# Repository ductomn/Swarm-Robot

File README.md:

# Swarm Robot Platform

A low-cost, scalable swarm robotic platform designed for research and educational purposes, capable of infrared (IR)-based communication and basic cooperative behaviors.

Playlist of videos showcasing robots and algorithms: https://www.youtube.com/playlist?list=PLNTM9zCJujTltedypfpow2rPiPkVAqfGI

---

## 🧠 About the Project

This project focuses on the design of a **cooperative robotic platform** built around the ESP32 microcontroller. The primary goal is to enable simple, local communication and decentralized coordination among identical robots, forming a **swarm**.

**Key design constraints:**
- Minimal production cost (~24 EUR/robot, parts only)
- Compact and robust mechanical design
- Infrared-based full-duplex communication (360°)
- Modular and scalable C firmware using ESP-IDF
- Developed as part of a Bachelor’s Thesis at Brno University of Technology

> **Thesis Title:**  
> *Návrh a realizace kooperativní robotické platformy s jednoduchou komunikací*  
> (*Design and Implementation of a Cooperative Robotic Platform with Simple Communication*)

---

## ⚙️ Features

### 🔁 360° IR Communication
6 pairs of IR LEDs and phototransistors evenly placed around the robot enable full directional communication.

### 🚧 Obstacle Detection
2 front-facing IR LED + phototransistor pairs detect obstacles.

### 🤖 Cooperative Algorithms

#### With Leader
- Simulates a robot "calling" others to complete a task.
- Modified CSMA/CA protocol ensures robots check for ongoing transmissions before broadcasting.
- Robots walk randomly looking for signals:
  - If signal is found in a randomly chosen time window → the robot becomes a **follower**.
  - If not → the robot becomes a **leader**.
- **Leader** can be pre-set (WITH_LEADER 1)

- **Flowchart of system with leader:**

- **Implemented algorithms:**

  - **Follow**  
    Followers track the leader, who moves randomly.  

  - **Spread Out**  
    Leader stays in place and acts as a beacon. Followers spread and return.  

#### Without Leader
- No signal detection or leader election.
- Algorithms run immediately after power-on.
  
- **Implemented algorithms:**

  - **Follow Chain**  
    Robots follow each other in a line. First robot walks randomly. Predefined or dynamic ID (order) assignment.  

  - **Chain**  
    Robots stay still in a line. The last robot moves forward to the front.  

### 🧠 FSM-Controlled Behavior

Each robot uses a finite state machine (FSM) for autonomous control and decision-making. The diagram shows the flow of states of algorithms with leader.  

### 🔧 Firmware Modules

- `io_define` – I/O pin mappings, robot ID
- `servo_driver` – movement (servo) control
- `led_driver` – IR LED driver
- `hwtimer` – Hardware timer driver
- `adc_lib` – ADC driver
- `dm_comm` – IR communication (Manchester encoding, CSMA/CA)
- `coop` – Cooperative algorithm logic
- `state_machine` – FSM and behavior transitions

---

## 🛠️ Setting Up

### Requirements

- [ESP-IDF](https://docs.espressif.com/projects/esp-idf/en/latest/esp32/)
- PlatformIO (recommended; VS Code plugin)  
  Target board: `ESP32DOIT-DEVKIT-V1`
- USB-to-UART bridge (e.g. CP2102)

### 🔧 Calibration  

- **Movement Calibration**  
  The robot doesn’t use encoders, so the motors may spin at different speeds, causing drift.  
  Adjust `SERVO_FORWARD_LEFT_MOD` and `SERVO_BACKWARDS_RIGHT_MOD` in `io_define.h` to straighten movement.

- **IR Signal Thresholds**  
  Tune `SIG_THRESHOLD` in `dm_comm.h` and `DIS_THRESHOLD` in `coop.h` to adjust signal sensitivity.

- **Algorithm Selection**  
  Some algorithms (like **Chain** or **Follow Chain**) should start immediately on power-up.  
  Define the startup behavior by setting flags to "1" (`CHAIN` or `FOLLOW_CHAIN`).

### ⚡ Flashing Instructions  

1. Connect the robot to your computer via USB.
2. Open `io_define.h` and set:
   - `ROBOT_ID` – unique number per robot
   - `WITH_LEADER` – `1` (for pre-set leader - ID1) or `0`
   - `CHAIN` or `FOLLOW_CHAIN` – chosen algorithm
3. Build and flash the firmware

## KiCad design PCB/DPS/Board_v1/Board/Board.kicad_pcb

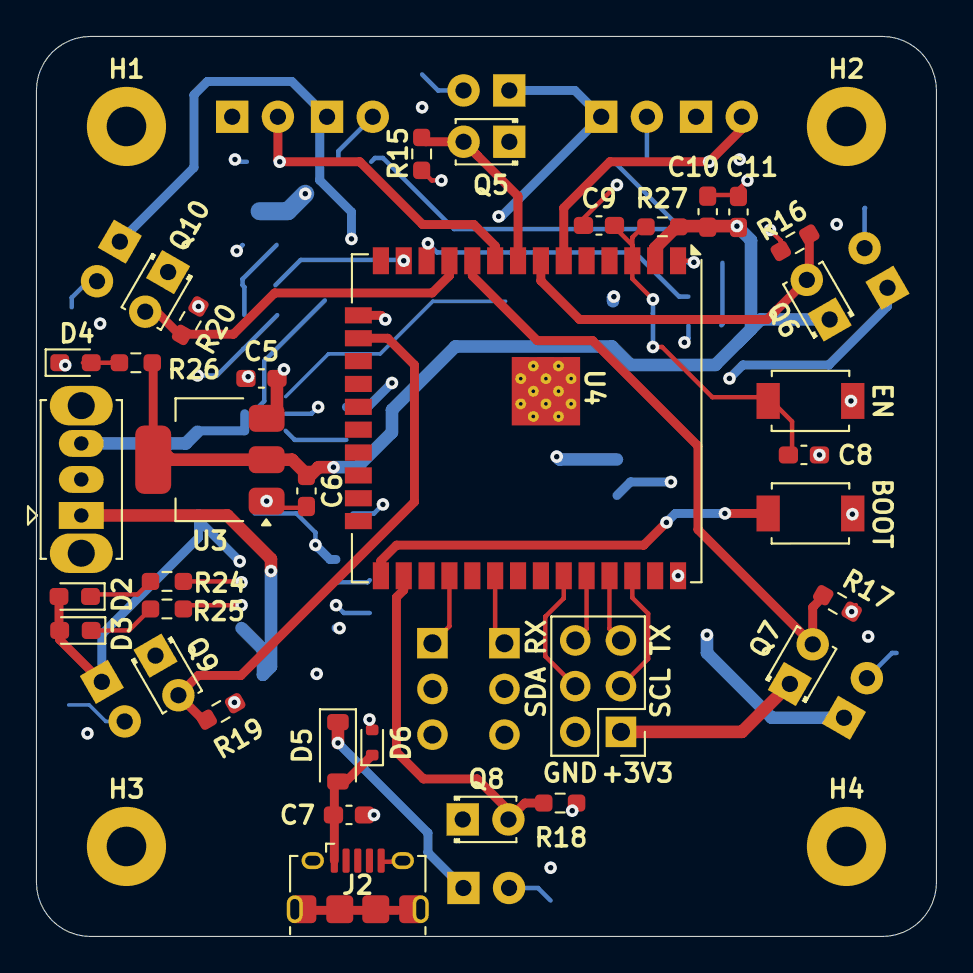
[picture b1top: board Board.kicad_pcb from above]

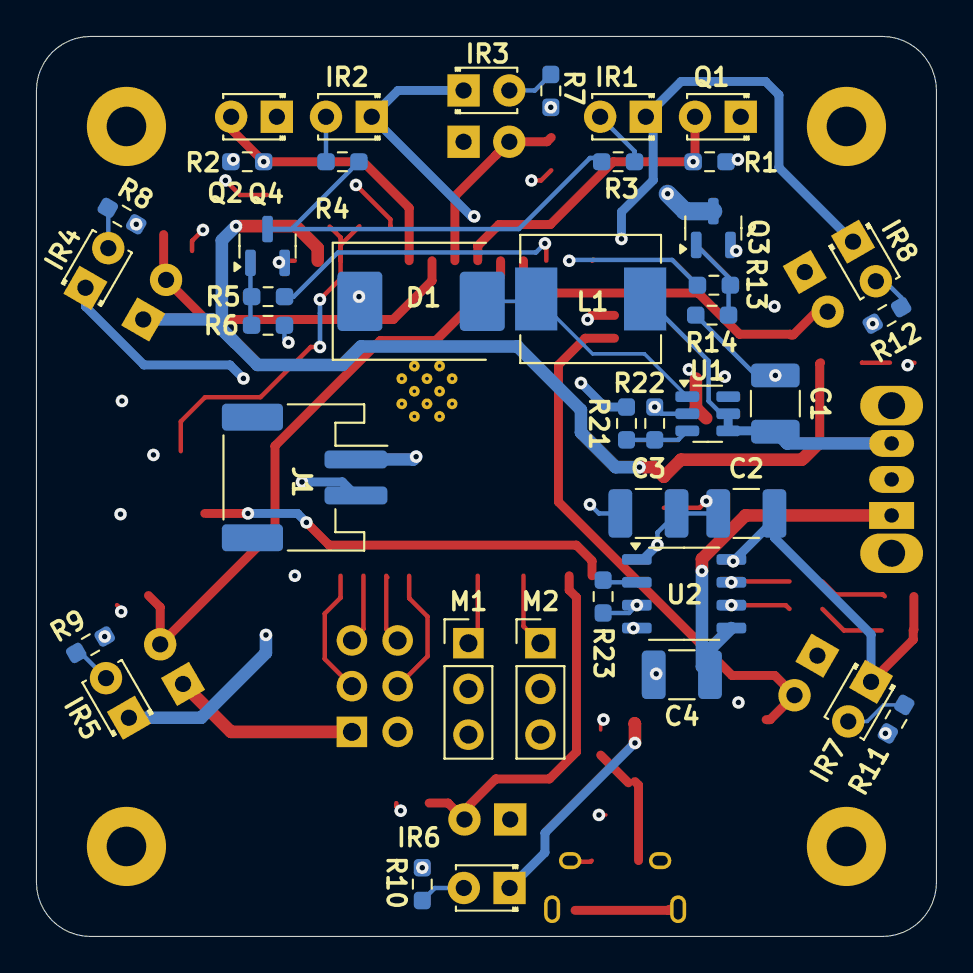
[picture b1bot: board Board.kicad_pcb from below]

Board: 4 copper layers, 50.0 x 50.0 mm, 79 parts (40 on the bottom side), 45 nets.

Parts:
BOOT: TS-1088R-02026; SW_Tactile_TS-1088R-02026
C1, C2: 22uF; C_1210_3225Metric_Pad1.33x2.70mm_HandSolder
C3, C4: 10uF; C_1210_3225Metric_Pad1.33x2.70mm_HandSolder
C5, C6: 10uF; C_0603_1608Metric_Pad1.08x0.95mm_HandSolder
C7, C8, C9, C11: 0.1uF; C_0603_1608Metric_Pad1.08x0.95mm_HandSolder
C10: 22uF; C_0603_1608Metric_Pad1.08x0.95mm_HandSolder
Comms1: PinHeader_2x03_P2.54mm_Vertical
D1: D_Schottky; D_SMC
D2: LED_RED; LED_0603_1608Metric_Pad1.05x0.95mm_HandSolder
D3: LED_GREEN; LED_0603_1608Metric_Pad1.05x0.95mm_HandSolder
D4: LED; LED_0603_1608Metric_Pad1.05x0.95mm_HandSolder
D5: 1N5819HW-7-F; D_SOD-123
D6: ESD5Z5.0T1G; D_SOD-523
EN: TS-1088R-02026; SW_Tactile_TS-1088R-02026
H1, H2, H3, H4: MountingHole_Pad; MountingHole_2.2mm_M2_Pad
IR1, IR2: SFH4544; LED_D1.8mm_W3.3mm_H2.4mm
IR3, IR4, IR5, IR6, IR7, IR8: OED-EL-1L2; LED_D1.8mm_W3.3mm_H2.4mm
J1: Li-Po 3.7V; JST_PH_S2B-PH-SM4-TB_1x02-1MP_P2.00mm_Horizontal
J2: USB_B_Micro; USB_Micro-B_Amphenol_10118194_Horizontal
L1: 4.7uH; L_Chilisin_BMRx00060630
M1, M2: SG90; PinHeader_1x03_P2.54mm_Vertical
Q1, Q2, Q5, Q6, Q7, Q8, Q9, Q10: TEFT4300; LED_D1.8mm_W3.3mm_H2.4mm
Q3, Q4: SI2312CDS; SOT-23
R1, R2, R15, R16, R17, R18, R19, R20: 4k7; R_0603_1608Metric_Pad0.98x0.95mm_HandSolder
R3, R4, R7, R8, R9, R10, R11, R12: 39; R_0603_1608Metric_Pad0.98x0.95mm_HandSolder
R5, R13: 100; R_0603_1608Metric_Pad0.98x0.95mm_HandSolder
R6, R14: 47k; R_0603_1608Metric_Pad0.98x0.95mm_HandSolder
R21: 16k; R_0603_1608Metric_Pad0.98x0.95mm_HandSolder
R22: 2k2; R_0603_1608Metric_Pad0.98x0.95mm_HandSolder
R23: 1k2; R_0603_1608Metric_Pad0.98x0.95mm_HandSolder
R24, R25: 1k; R_0603_1608Metric_Pad0.98x0.95mm_HandSolder
R26: 5k1; R_0603_1608Metric_Pad0.98x0.95mm_HandSolder
R27: 10k; R_0603_1608Metric_Pad0.98x0.95mm_HandSolder
SW1: SLW-864574-5A-RA-N-D; SW_Slide_SPDT_Straight_CK_OS102011MS2Q
U1: MT3608; SOT-23-6
U2: TP4056; SOP-8_3.9x4.9mm_P1.27mm
U3: AMS1117-3.3; SOT-223-3_TabPin2
U4: ESP32-WROOM-32UE

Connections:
+3V3: C6.1, C10.1, C11.1, Comms1.1 (VCC), Q1.1 (C), Q2.1 (C), Q5.1 (C), Q6.1 (C), Q7.1 (C), Q8.1 (C), Q9.1 (C), Q10.1 (C), R26.1, R27.1, U3.2 (VO), U4.2 (VDD)
+5V: C2.1, C3.1, C5.1, D1.1 (K), D2.2 (A), D3.2 (A), D5.1 (K), IR1.1 (K), IR2.1 (K), IR3.1 (K), IR4.1 (K), IR5.1 (K), IR6.1 (K), IR7.1 (K), IR8.1 (K), M1.2 (+), M2.2 (+), R21.1, U2.4 (VCC), U2.8 (CE), U3.3 (VI)
/ESP32/EN: C8.1, C9.1, EN.2, R27.2, U4.3 (EN)
/ESP32/IO0_BTN: BOOT.2, U4.25 (IO0)
A0: Q5.2 (E), R15.2, U4.8 (IO32)
A1: Q6.2 (E), R16.2, U4.7 (IO35)
A2: Q7.2 (E), R17.2, U4.10 (IO25)
A3: Q8.2 (E), R18.2, U4.26 (IO4)
A4: Q9.2 (E), R19.2, U4.16 (IO13)
A5: Q10.2 (E), R20.2, U4.11 (IO26)
A8_DIS: Q1.2 (E), R1.2, U4.9 (IO33)
A9_DIS: Q2.2 (E), R2.2, U4.6 (IO34)
CHRG_B+: C4.1, SW1.1 (A), U2.5 (BAT)
GND: BOOT.1, C1.2, C2.2, C3.2, C4.2, C5.2, C6.2, C7.2, C8.2, C9.2, C10.2, C11.2, Comms1.2 (GND), D4.1 (K), D6.2 (A), EN.1, H1.1, H2.1, H3.1, H4.1, J1.2, J2.5 (GND), J2.6 (Shield), M1.3 (-), M2.3 (-), Q3.2 (S), Q4.2 (S), R1.1, R2.1, R6.1, R14.1, R15.1, R16.1, R17.1, R18.1, R19.1, R20.1, R22.2, R23.1, U1.2 (GND), U2.1 (TEMP), U2.3 (GND), U3.1 (GND), U4.1 (GND), U4.15 (GND), U4.38 (GND), U4.39 (GND)
IR_DIS: R5.1, U4.12 (IO27)
IR_SIG: R13.1, U4.13 (IO14)
IR_V: Q3.3 (D), R7.1, R8.1, R9.1, R10.1, R11.1, R12.1
IR_V_DIS: Q4.3 (D), R3.1, R4.1
unnamed: D1.2 (A), L1.2, U1.1 (SW)
unnamed: D2.1 (K), R24.2
unnamed: D3.1 (K), R25.2
unnamed: D4.2 (A), R26.2
unnamed: IR1.2 (A), R3.2
unnamed: IR2.2 (A), R4.2
unnamed: IR3.2 (A), R7.2
unnamed: IR4.2 (A), R8.2
unnamed: IR5.2 (A), R9.2
unnamed: IR6.2 (A), R10.2
unnamed: IR7.2 (A), R11.2
unnamed: IR8.2 (A), R12.2
unnamed: Q3.1 (G), R13.2, R14.2
unnamed: Q4.1 (G), R5.2, R6.2
unnamed: J1.1, SW1.2 (B)
unnamed: C1.1, L1.1, SW1.3 (C), U1.4 (EN), U1.5 (IN)
unnamed: R21.2, R22.1, U1.3 (FB)
unnamed: R24.1, U2.7 (CHRG)
unnamed: R23.2, U2.2 (PROG)
unnamed: R25.1, U2.6 (STDBY)
PWM_A: M1.1 (PWM), U4.30 (IO18)
PWM_B: M2.1 (PWM), U4.28 (IO17)
RX: Comms1.6 (TX), U4.34 (RXD0/IO3)
SCL: Comms1.3 (SCL), U4.36 (IO22)
SDA: Comms1.4 (SDA), U4.33 (IO21)
TX: Comms1.5 (RX), U4.35 (TXD0/IO1)
VBUS: C7.1, D5.2 (A), D6.1 (K), J2.1 (VBUS)

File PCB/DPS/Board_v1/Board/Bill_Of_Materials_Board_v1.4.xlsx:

Reference | Value | Datasheet | Footprint | Qty | DNP | Total
C1,C2 | 22uF | ~ | -- mixed values -- | 2 | x | 0 |  | Laskakit
L1 | 4.7uH | ~ | Inductor_SMD:L_Chilisin_BMRx00060630 | 1 | x | 0 |  | Mouser
D1 | D_Schottky | ~ | Diode_SMD:D_SMC | 1 | x | 0
J2 | USB_B_Micro | ~ | Connector_USB:USB_Micro-B_Amphenol_10118194-0001LF_Horizontal | 1 | x | 0
R22 | 2k2 | ~ | Capacitor_SMD:C_0603_1608Metric_Pad1.08x0.95mm_HandSolder | 1 | x | 0 |  | TOTAL:
U1 | MT3608 | https://www.olimex.com/Products/Breadboarding/BB-PWR-3608/re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 | Package_TO_SOT_SMD:SOT-23-6 | 1 | x | 0 |  |  | 610.24900000000002
C3,C4 | 10uF | ~ | -- mixed values -- | 2 | x | 0
R23 | 1k2 | ~ | Capacitor_SMD:C_0603_1608Metric_Pad1.08x0.95mm_HandSolder | 1 | x | 0
R24,R25 | 1k | ~ | -- mixed values -- | 2 | x | 0
D2 | LED_RED | ~ | LED_SMD:LED_0603_1608Metric_Pad1.05x0.95mm_HandSolder | 1 | x | 0
D3 | LED_GREEN | ~ | LED_SMD:LED_0603_1608Metric_Pad1.05x0.95mm_HandSolder | 1 | x | 0
U2 | TP4056 | https://eu.mouser.com/datasheet/2/830/TP4056-2487427.pdf | Package_SO:SOP-8_3.9x4.9mm_P1.27mm | 1 | 18 | 18
C5, C6 | 10uF | ~ | 0603_1608 | 2 | 1.1299999999999999 | 2.2599999999999998 | x
C7,C8,C9,C11 | 0.1uF | ~ | Capacitor_SMD:C_0603_1608Metric_Pad1.08x0.95mm_HandSolder | 4 | 0.376 | 1.504 | x
C10 | 22uF | ~ | Capacitor_SMD:C_0603_1608Metric_Pad1.08x0.95mm_HandSolder | 1 | 1.75 | 1.75 | x
Comms1 | ~ |  | Connector_PinHeader_2.54mm:PinHeader_2x03_P2.54mm_Vertical | 1 | 3 | 3
D6 | ESD5Z5.0T1G | https://www.onsemi.com/pdf/datasheet/esd5z2.5t1-d.pdf | Diode_SMD:D_SOD-523 | 1 | 3.33 | 3.33 | x
D5 | 1N5819HW-7-F | ~ | Diode_SMD:D_SOD-123 | 1 | 5.96 | 5.96 | x
D4 | LED | ~ | LED_SMD:LED_0603_1608Metric_Pad1.05x0.95mm_HandSolder | 1 | 0.8 | 0.8 | x
IR1,IR2 | SFH4544 | ~ | LED_THT:LED_D1.8mm_W3.3mm_H2.4mm | 2 | 13.33 | 26.66 | x
IR3,IR4,IR5,IR6,IR7,IR8 | SFH4547 | ~ | LED_THT:LED_D1.8mm_W3.3mm_H2.4mm | 6 | 6.57 | 39.42 | x
J1 | Li-Po 3.7V_1000mAh |  | Connector_JST:JST_PH_S2B-PH-SM4-TB_1x02-1MP_P2.00mm_Horizontal | 1 | 99 | 99 | x
 | Konektor _Baterie |  |  | 1 | 2 | 2 | x
M1,M2 | Servo_Motor SG90 | ~ |  | 2 | 60 | 120 | x
 | Konektor |  | Connector_PinHeader_2.54mm:PinHeader_1x03_P2.54mm_Vertical | 2 | 0.8 | 1.6
Q5,Q6,Q7,Q8,Q9,Q10 | TEFT4300 | https://www.rcscomponents.kiev.ua/datasheets/bpw40.pdf | LED_THT:LED_D1.8mm_W3.3mm_H2.4mm | 6 | 9.3000000000000007 | 55.800000000000004 | x
Q1,Q2 | 304PTD4B-1A |  |  | 2 | 2.8 | 5.6
Q3,Q4 | SI2312CDS | ~ | Package_TO_SOT_SMD:SOT-23 | 2 | 3.8 | 7.6 | x
R1,R2,R15,R16,R17,R18,R19,R20 | 4k7 | ~ | Resistor_SMD:R_0603_1608Metric_Pad0.98x0.95mm_HandSolder | 8 | 0.376 | 3.008 | x
R3,R4,R7,R8,R9,R10,R11,R12 | 39 | ~ | Resistor_SMD:R_0603_1608Metric_Pad0.98x0.95mm_HandSolder | 8 | 0.32600000000000001 | 2.6080000000000001 | x
R5,R13 | 100 | ~ | Resistor_SMD:R_0603_1608Metric_Pad0.98x0.95mm_HandSolder | 2 | 0.2 | 0.4 | x
R6,R14 | 47k | ~ | Resistor_SMD:R_0603_1608Metric_Pad0.98x0.95mm_HandSolder | 2 | 0.22600000000000001 | 0.45200000000000001 | x
R21 | 16k | ~ | Capacitor_SMD:C_0603_1608Metric_Pad1.08x0.95mm_HandSolder | 1 | 0.2 | 0 | x
R27 | 10k | ~ | Resistor_SMD:R_0603_1608Metric_Pad0.98x0.95mm_HandSolder | 1 | 0.30099999999999999 | 0.30099999999999999 | x
R26 | 5k1 | ~ | Resistor_SMD:R_0603_1608Metric_Pad0.98x0.95mm_HandSolder | 1 | 0.32600000000000001 | 0.32600000000000001 | x
SW1 | SLW-864574-5A-RA-N-D | ~ | Button_Switch_THT:SW_Slide_SPDT_Straight_CK_OS102011MS2Q | 1 | 7.87 | 7.87 | x
SW2,SW3 | TS-1088R-02026 | ~ | 0_Custom_Footprints:SW_Tactile_TS-1088R-02026 | 2 | 3 | 6 | x
U3 | AMS1117-3.3 | http://www.advanced-monolithic.com/pdf/ds1117.pdf | Package_TO_SOT_SMD:SOT-223-3_TabPin2 | 1 | 3 | 3 | x
U4 | ESP32-WROOM-32UE | https://www.espressif.com/sites/default/files/documentation/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 | RF_Module:ESP32-WROOM-32D | 1 | 68 | 68 | x
kolo sg90 |  |  |  | 2 | 38 | 76 | x
podperné kolo |  |  |  | 2 | 24 | 48 | x
 |  |  |  | 82

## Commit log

2025-05-22 Initial commit - uploading done code
2025-05-23 Added 3D model
2025-05-23 Added PCB files
2025-05-23 Added images/photos
2025-06-20 Added videos
2025-06-20 Update README.md
    Described project
2025-06-20 changed chosen algorithms to random between COMMAND1 and COMMAND2
    fixed state_command_clear() to not clear COMMAND3
2026-01-28 Add video playlist link to README
    Added a playlist link for videos showcasing robots and algorithms.
